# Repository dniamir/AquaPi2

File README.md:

# AquaPi Smart Aquarium
A Raspberry Pi project that uses 3 features to monitor an aquarium:
- Level sensor for determining water level
- Waterproof temperature sensor for monitoring the aquarium temperature
- Pump system for pumping out dirty water and pumping in fresh water

## Summary
This code utlizies high level functions to communicate with sensors and set their configuration for proper monitoring of an aquarium.

Unfortunately, I can't make the sub-repository for chip communication public. However that package provides a simple interface for communicating with sensors va I2C and SPI.

Another feature I considered adding was a home-made water quality sensor using a custom AFE and a LED/diode combination. This is still a WIP.

MIT License

Copyright (c) 2020 Engineering Outdoors

Permission is hereby granted, free of charge, to any person obtaining a copy
of this software and associated documentation files (the "Software"), to deal
in the Software without restriction, including without limitation the rights
to use, copy, modify, merge, publish, distribute, sublicense, and/or sell
copies of the Software, and to permit persons to whom the Software is
furnished to do so, subject to the following conditions:

The above copyright notice and this permission notice shall be included in all
copies or substantial portions of the Software.

THE SOFTWARE IS PROVIDED "AS IS", WITHOUT WARRANTY OF ANY KIND, EXPRESS OR
IMPLIED, INCLUDING BUT NOT LIMITED TO THE WARRANTIES OF MERCHANTABILITY,
FITNESS FOR A PARTICULAR PURPOSE AND NONINFRINGEMENT. IN NO EVENT SHALL THE
AUTHORS OR COPYRIGHT HOLDERS BE LIABLE FOR ANY CLAIM, DAMAGES OR OTHER
LIABILITY, WHETHER IN AN ACTION OF CONTRACT, TORT OR OTHERWISE, ARISING FROM,
OUT OF OR IN CONNECTION WITH THE SOFTWARE OR THE USE OR OTHER DEALINGS IN THE
SOFTWARE.

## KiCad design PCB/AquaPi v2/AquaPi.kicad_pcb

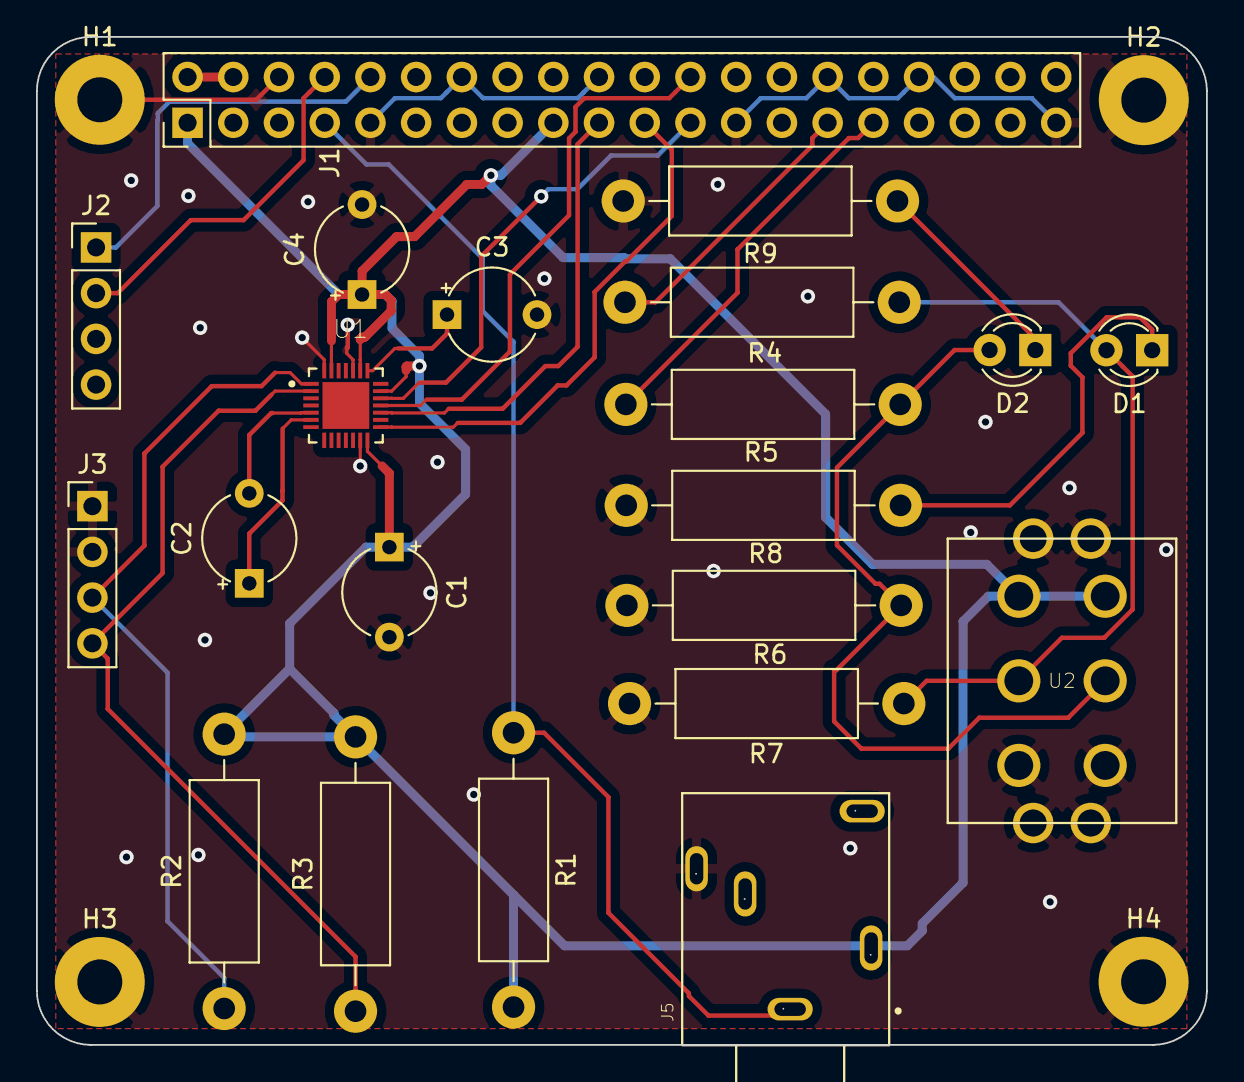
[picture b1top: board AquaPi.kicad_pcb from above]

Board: 2 copper layers, 65.0 x 56.0 mm, 25 parts (0 on the bottom side), 21 nets.

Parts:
C1, C3, C4: 100nF; CP_Radial_Tantal_D5.0mm_P5.00mm
C2: 1nF; CP_Radial_Tantal_D5.0mm_P5.00mm
D1, D2: LED; LED_D3.0mm
H1, H2, H3, H4: MountingHole_Pad; MountingHole_2.5mm_Pad
J1: Raspberry_Pi_2_3; PinHeader_2x20_P2.54mm_Vertical
J2, J3: Conn_01x04_Female; PinHeader_1x04_P2.54mm_Vertical
J5: 35RAPC4BH3; SWITCHCRAFT_35RAPC4BH3
R1: 4.7k; R_Axial_DIN0411_L9.9mm_D3.6mm_P15.24mm_Horizontal
R2, R3: 1.5k; R_Axial_DIN0411_L9.9mm_D3.6mm_P15.24mm_Horizontal
R4, R5: 1.2k; R_Axial_DIN0411_L9.9mm_D3.6mm_P15.24mm_Horizontal
R6, R7: 12k; R_Axial_DIN0411_L9.9mm_D3.6mm_P15.24mm_Horizontal
R8, R9: 2k; R_Axial_DIN0411_L9.9mm_D3.6mm_P15.24mm_Horizontal
U1: MAX11410ATI+; QFN40P400X400X80-29N
U2: M2022LL2W13

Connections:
/3.3V: C1.1, C4.1, J1.1, J1.17, J5.5, R1.2, R2.2, R3.2, U1.14, U1.20, U1.23, U1.27, U2.P3, U2.P6
/5V: J1.2, J1.4
/GPIO5: J1.29, R4.1
/GPIO6: J1.31, R5.1
/MAX11410_CS: J1.24, U1.18
/MAX11410_MISO: J1.21, U1.15
/MAX11410_MOSI: J1.19, U1.17
/MAX11410_SLCK: J1.23, U1.19
/eTape_Sense+: J3.4, R3.1, U1.2
/eTape_Sense-: J3.3, R2.1, U1.1
GND: C1.2, C3.2, C4.2, H1.1, H2.1, H3.1, H4.1, J1.6, J1.9, J1.14, J1.20, J1.25, J1.30, J1.34, J1.39, J3.1, J3.2, J5.2, R6.1, R7.1, R8.1, R9.2, U1.13, U1.24, U1.28, U2.GND1, U2.GND2, U2.GND3, U2.GND4, U2.P1, U2.P4
unnamed: C2.1, U1.6
unnamed: C2.2, U1.5
unnamed: C3.1, U1.22
unnamed: D1.1, R8.2
unnamed: D1.2, R4.2, R7.2, U2.P2
unnamed: D2.1, R9.1
unnamed: D2.2, R5.2, R6.2, U2.P5
unnamed: J1.7, J5.1, R1.1
unnamed: J1.8, J2.2
unnamed: J1.10, J2.1

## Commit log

2020-12-13 Initial commit of AquaPi and PCB
2020-12-13 Fix readme title
